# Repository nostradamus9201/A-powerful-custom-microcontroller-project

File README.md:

# A-powerful-custom-microcontroller-project
An Rp2354B based microcontroller with more storage and more ports, designed and traced by yours truly.
It consists of 6 layers, one male and one female usb c port, and onboard memory with 2 extra 16mb flash chips.

#Pitch:
Ever tired of having to find an outdated usb micro-b connector to connect to your devboard ?
Fear not.
Ever tired of having too little flash memory ?
Feaaar noot.
Ever tired of ANY issue with your rp2350 devboards ?
The "Just a better rp2354 devboard"™   is here to fix all of them.
(Not guranteed to fix all of your problems, no refunds)

# Part Images and Schematics

All layers combined

Front layer

GND layer

3v3 power layer

1v1 & misc. layer

Misc. layer

Back layer

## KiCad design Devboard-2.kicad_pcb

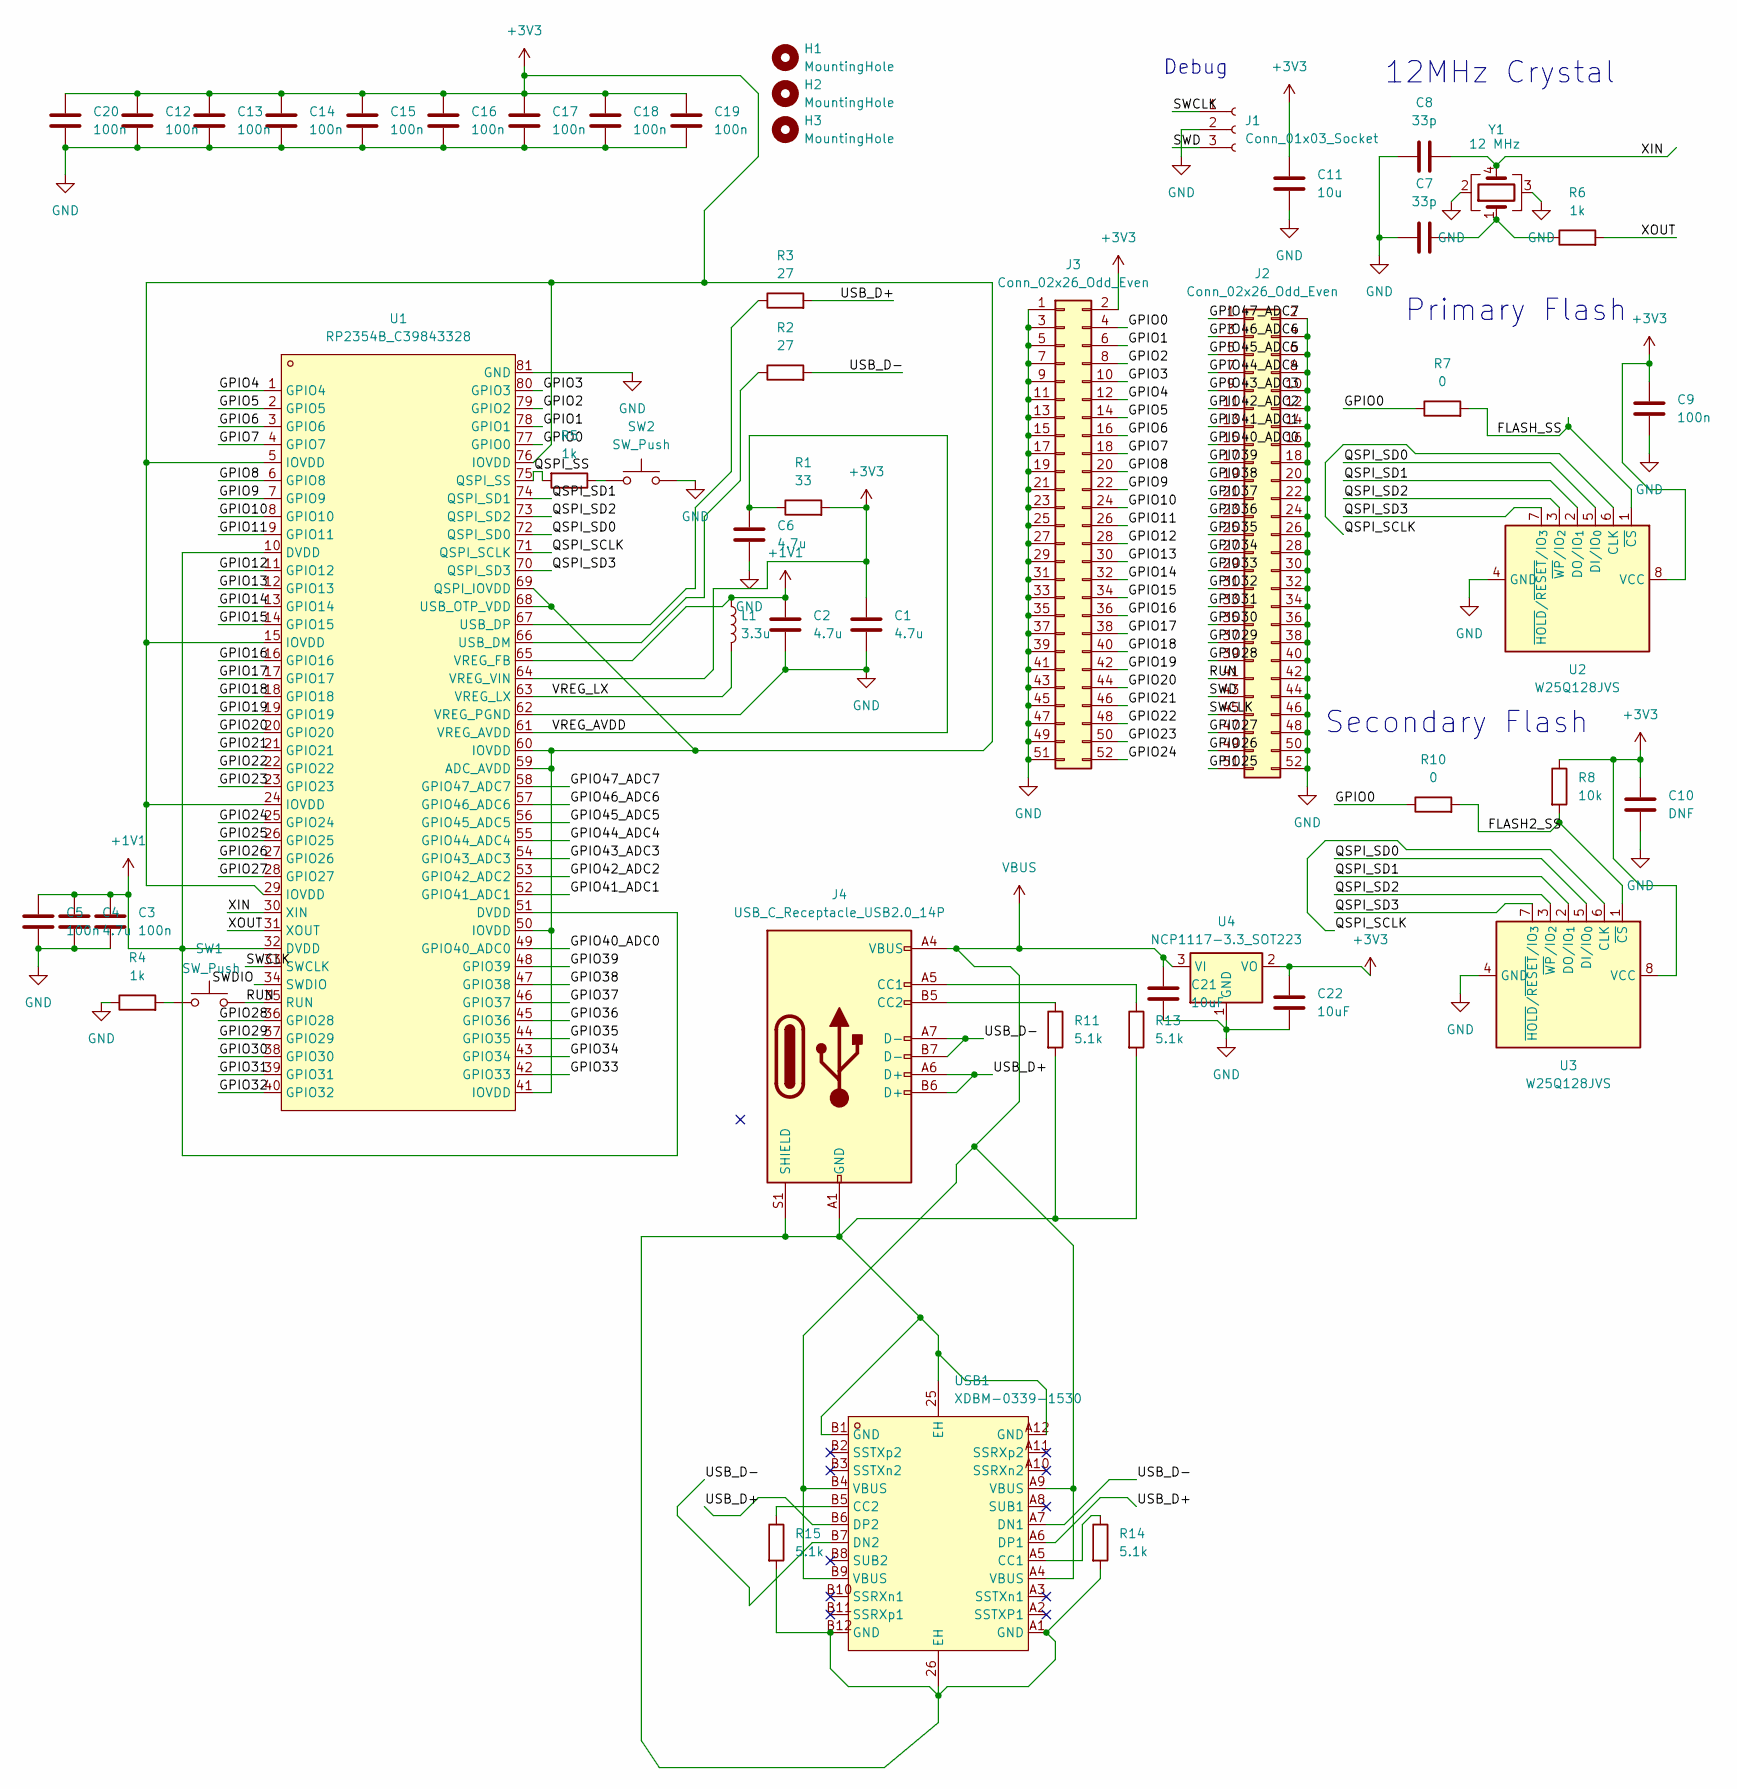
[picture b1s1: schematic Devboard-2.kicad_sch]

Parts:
C1, C2, C4, C6: 4.7u; C_0603_1608Metric
C3, C5, C9, C12, C13, C14, C15, C16, C17, C18, C19, C20: 100n; C_0402_1005Metric
C7, C8: 33p; C_0402_1005Metric
C10: DNF; C_0402_1005Metric
C11: 10u; C_0603_1608Metric
C21, C22: 10uF; C_0603_1608Metric
H1, H2, H3: MountingHole; MountingHole_2.1mm
J1: Conn_01x03_Socket; PinHeader_1x03_P2.54mm_Vertical
J2, J3: Conn_02x26_Odd_Even; PinHeader_2x26_P2.54mm_Vertical
J4: USB_C_Receptacle_USB2.0_14P; USB_C_Receptacle_HRO_TYPE-C-31-M-12
L1: 3.3u; C_0805_2012Metric
R1: 33; R_0402_1005Metric
R2, R3: 27; R_0402_1005Metric
R4, R5, R6: 1k; R_0402_1005Metric
R7, R10: 0; R_0402_1005Metric
R8: 10k; R_0402_1005Metric
R11, R13, R14, R15: 5.1k; R_0402_1005Metric
SW1, SW2: SW_Push; SW_Push_SPST_NO_Alps_SKRK
U1: RP2354B_C39843328; QFN-80_L10.0-W10.0-P0.40-TL-EP3.4; LCSC Part C39843328
U2, U3: W25Q128JVS; SOIC-8_5.3x5.3mm_P1.27mm
U4: NCP1117-3.3_SOT223; SOT-223-3_TabPin2
USB1: XDBM-0339-1530; USB-C-SMD_USB-3.1-C-TYPE; LCSC Part C7527710
Y1: 12 MHz; Crystal_SMD_3225-4Pin_3.2x2.5mm

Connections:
+1V1: C2.1, C3.1, C4.1, C5.1, L1.1, U1.10 (DVDD), U1.32 (DVDD), U1.51 (DVDD), U1.65 (VREG_FB)
+3V3: C1.1, C9.1, C10.1, C11.1, C12.1, C13.1, C14.1, C15.1, C16.1, C17.1, C18.1, C19.1, C20.1, C22.1, J3.2, R1.2, R8.1, U1.5 (IOVDD), U1.15 (IOVDD), U1.24 (IOVDD), U1.29 (IOVDD), U1.41 (IOVDD), U1.50 (IOVDD), U1.59 (ADC_AVDD), U1.60 (IOVDD), U1.64 (VREG_VIN), U1.68 (USB_OTP_VDD), U1.69 (QSPI_IOVDD), U1.76 (IOVDD), U2.8 (VCC), U3.8 (VCC), U4.2 (VO)
/FLASH2_SS: R8.2, R10.2, U3.1 (~CS)
/FLASH_SS: R7.2, U2.1 (~CS)
/GPIO0: J3.4, R7.1, R10.1, U1.77 (GPIO0)
/GPIO1: J3.6, U1.78 (GPIO1)
/GPIO2: J3.8, U1.79 (GPIO2)
/GPIO3: J3.10, U1.80 (GPIO3)
/GPIO4: J3.12, U1.1 (GPIO4)
/GPIO5: J3.14, U1.2 (GPIO5)
/GPIO6: J3.16, U1.3 (GPIO6)
/GPIO7: J3.18, U1.4 (GPIO7)
/GPIO8: J3.20, U1.6 (GPIO8)
/GPIO9: J3.22, U1.7 (GPIO9)
/GPIO10: J3.24, U1.8 (GPIO10)
/GPIO11: J3.26, U1.9 (GPIO11)
/GPIO12: J3.28, U1.11 (GPIO12)
/GPIO13: J3.30, U1.12 (GPIO13)
/GPIO14: J3.32, U1.13 (GPIO14)
/GPIO15: J3.34, U1.14 (GPIO15)
/GPIO16: J3.36, U1.16 (GPIO16)
/GPIO17: J3.38, U1.17 (GPIO17)
/GPIO18: J3.40, U1.18 (GPIO18)
/GPIO19: J3.42, U1.19 (GPIO19)
/GPIO20: J3.44, U1.20 (GPIO20)
/GPIO21: J3.46, U1.21 (GPIO21)
/GPIO22: J3.48, U1.22 (GPIO22)
/GPIO23: J3.50, U1.23 (GPIO23)
/GPIO24: J3.52, U1.25 (GPIO24)
/GPIO25: J2.51, U1.26 (GPIO25)
/GPIO26: J2.49, U1.27 (GPIO26)
/GPIO27: J2.47, U1.28 (GPIO27)
/GPIO28: J2.39, U1.36 (GPIO28)
/GPIO29: J2.37, U1.37 (GPIO29)
/GPIO30: J2.35, U1.38 (GPIO30)
/GPIO31: J2.33, U1.39 (GPIO31)
/GPIO32: J2.31, U1.40 (GPIO32)
/GPIO33: J2.29, U1.42 (GPIO33)
/GPIO34: J2.27, U1.43 (GPIO34)
/GPIO35: J2.25, U1.44 (GPIO35)
/GPIO36: J2.23, U1.45 (GPIO36)
/GPIO37: J2.21, U1.46 (GPIO37)
/GPIO38: J2.19, U1.47 (GPIO38)
/GPIO39: J2.17, U1.48 (GPIO39)
/GPIO40_ADC0: J2.15, U1.49 (GPIO40_ADC0)
/GPIO41_ADC1: J2.13, U1.52 (GPIO41_ADC1)
/GPIO42_ADC2: J2.11, U1.53 (GPIO42_ADC2)
/GPIO43_ADC3: J2.9, U1.54 (GPIO43_ADC3)
/GPIO44_ADC4: J2.7, U1.55 (GPIO44_ADC4)
/GPIO45_ADC5: J2.5, U1.56 (GPIO45_ADC5)
/GPIO46_ADC6: J2.3, U1.57 (GPIO46_ADC6)
/GPIO47_ADC7: J2.1, U1.58 (GPIO47_ADC7)
/QSPI_SCLK: U1.71 (QSPI_SCLK), U2.6 (CLK), U3.6 (CLK)
/QSPI_SD0: U1.72 (QSPI_SD0), U2.5 (DI/IO_{0}), U3.5 (DI/IO_{0})
/QSPI_SD1: U1.74 (QSPI_SD1), U2.2 (DO/IO_{1}), U3.2 (DO/IO_{1})
/QSPI_SD2: U1.73 (QSPI_SD2), U2.3 (~WP/IO_{2}), U3.3 (~WP/IO_{2})
/QSPI_SD3: U1.70 (QSPI_SD3), U2.7 (~HOLD/~RESET/IO_{3}), U3.7 (~HOLD/~RESET/IO_{3})
/QSPI_SS: R5.2, U1.75 (QSPI_SS)
/RUN: J2.41, SW1.2, U1.35 (RUN)
/SWCLK: J1.1, J2.45, U1.33 (SWCLK)
/USB_D+: J4.A6 (D+), J4.B6 (D+), R3.2, USB1.A6 (DP1), USB1.B6 (DP2)
/USB_D-: J4.A7 (D-), J4.B7 (D-), R2.2, USB1.A7 (DN1), USB1.B7 (DN2)
/VREG_AVDD: C6.1, R1.1, U1.61 (VREG_AVDD)
/VREG_LX: L1.2, U1.63 (VREG_LX)
/XIN: C8.2, U1.30 (XIN), Y1.4
unnamed: J4.A5 (CC1), R13.1
unnamed: J4.B5 (CC2), R11.1
unnamed: R4.2, SW1.1
unnamed: R5.1, SW2.1
unnamed: R2.1, U1.66 (USB_DM)
unnamed: R3.1, U1.67 (USB_DP)
unnamed: R14.1, USB1.A5 (CC1)
unnamed: R15.1, USB1.B5 (CC2)
VBUS: C21.1, J4.A4 (VBUS), J4.A9 (VBUS), J4.B4 (VBUS), J4.B9 (VBUS), U4.3 (VI), USB1.A4 (VBUS), USB1.A9 (VBUS), USB1.B4 (VBUS), USB1.B9 (VBUS)

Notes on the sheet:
Debug
12MHz Crystal
Secondary Flash
Primary Flash

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
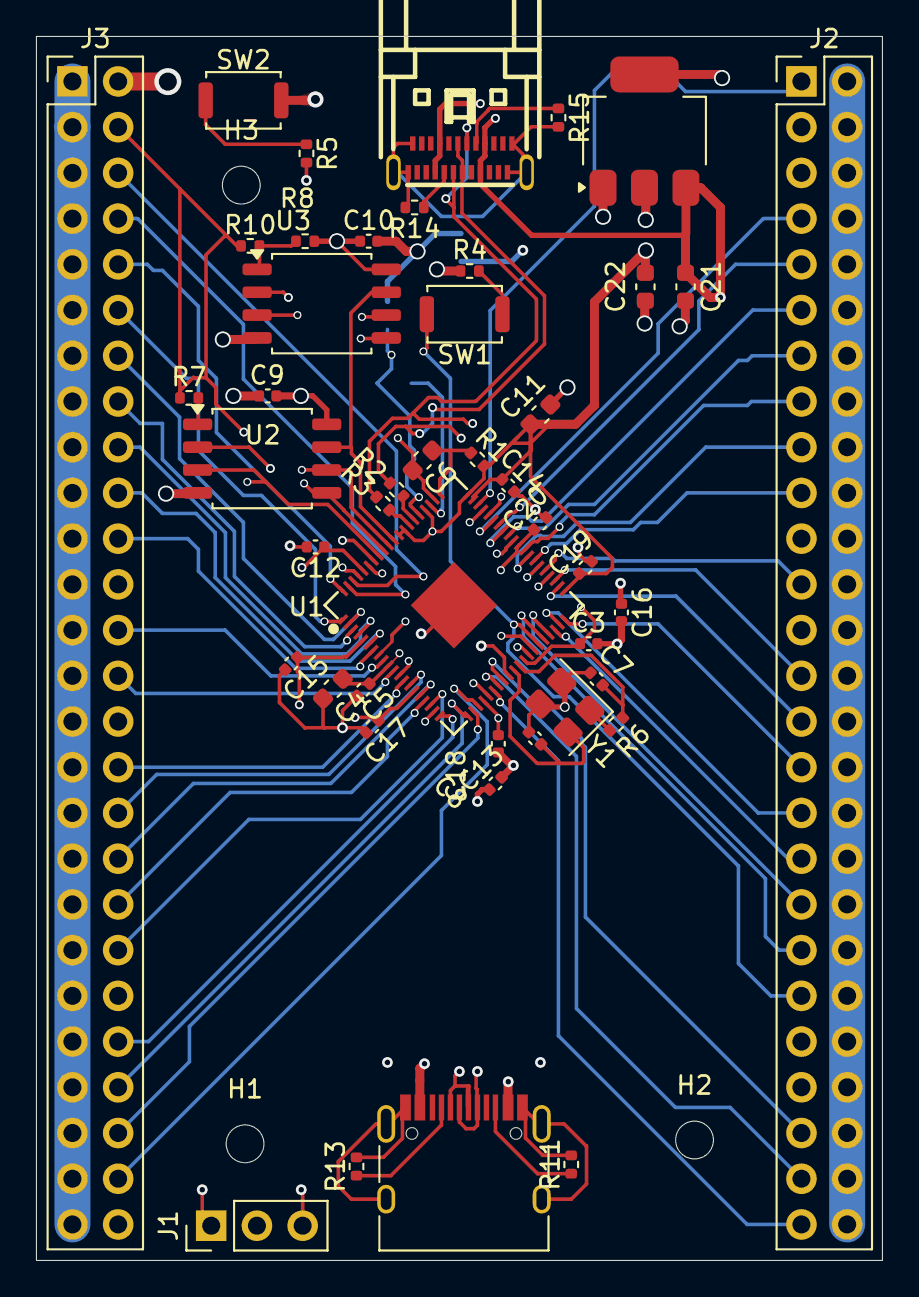
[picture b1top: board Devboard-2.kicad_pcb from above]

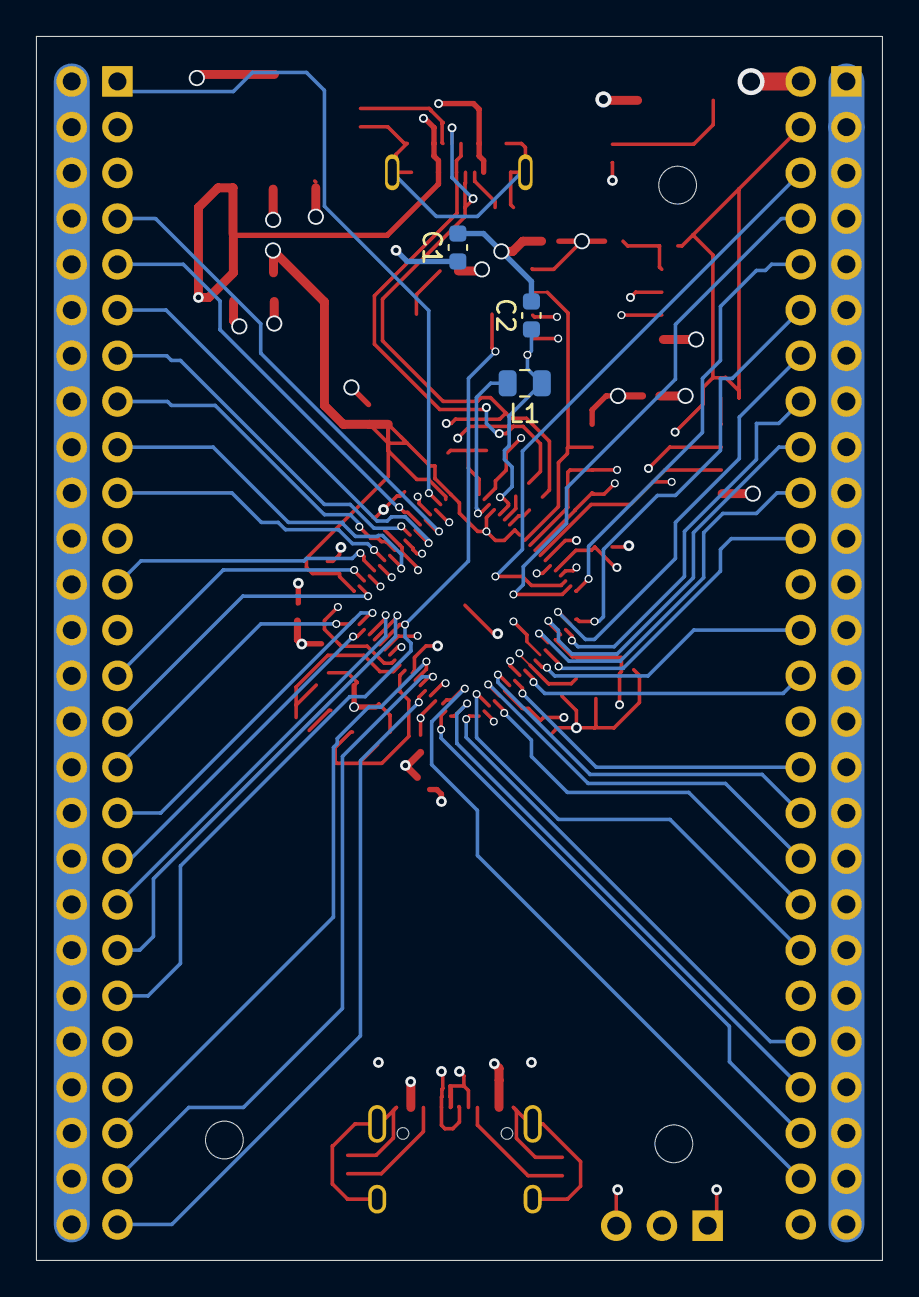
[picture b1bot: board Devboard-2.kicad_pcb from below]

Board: 6 copper layers, 47.0 x 68.0 mm, 51 parts (3 on the bottom side), 79 nets.
